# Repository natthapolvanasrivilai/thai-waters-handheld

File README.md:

# Thai Waters handheld

[**Current project status**](docs/wiki/Current-status.md) · [**Download the live interactive handbook**](https://github.com/natthapolvanasrivilai/thai-waters-handheld/releases/download/r0009-complete-fit-1/Thai-Waters-handbook.html) · [Hardware review PR #98](https://github.com/natthapolvanasrivilai/thai-waters-handheld/pull/98)

[Hardware closure and playtest issues](quality/hardware-gate.md) · [Product tracker](https://github.com/natthapolvanasrivilai/thai-waters-handheld/issues/1) · [November hardware review](quality/hardware-review-2026-11-23.md)

[Private touch playtest](https://thai-waters-pocket-angler.shoung0690.chatgpt.site) · [Builds and verification](docs/wiki/Software-and-tests.md#current-release) · [Clock and collection recovery](docs/wiki/Clock-and-saves.md)

[Hardware revisions and CAD](docs/wiki/Hardware-and-3D.md) · [One-unit BOM and price research](docs/wiki/BOM-and-business.md) · [Current release and hardware milestone](docs/wiki/Software-and-tests.md#current-release)

**[Browse the product wiki](docs/wiki/Home.md)** · **[Play on a phone](https://thai-waters-pocket-angler.shoung0690.chatgpt.site)**

[Rectangular PCB, revised mount and fit gauge](hardware/electronics/case-board-r0002/README.md) · [Open the new board review](https://github.com/natthapolvanasrivilai/thai-waters-handheld/releases/download/case-board-r0002-guide-2/Mount-review.html)

**Current PLA test print.** TW-A-0003-R0009 includes the rectangular PCB and matching case, all enclosure plastics and the PCB and component mockups. The 27 objects occupy eight plates for PolyTerra PLA on the X1 Carbon with a 0.4 mm nozzle and SuperTack. Physical fit awaits printing. [PolyTerra PLA X1C project](https://github.com/natthapolvanasrivilai/thai-waters-handheld/releases/download/r0009-complete-fit-1/Thai-Waters-R0009-Complete-Fit-PolyTerra-SuperTack-X1C.3mf) · [PLA print sequence and checks](hardware/mechanical/full-fit-r0009/README.md) · [Offline 3D assembly](https://github.com/natthapolvanasrivilai/thai-waters-handheld/releases/download/r0009-complete-fit-1/Enclosure-fit-guide.html)

Open the downloaded handbook in a browser. **Current status** checks this GitHub project on every open and links to the evidence for the selected revision. When the check fails, the handbook labels the dated snapshot saved with the file. The archived tabs still work offline. The [original R0011 handbook](https://github.com/natthapolvanasrivilai/thai-waters-handheld/releases/download/r0011-hardware-review-1/Thai-Waters-handbook.html) and [Rev F engineering release](https://github.com/natthapolvanasrivilai/thai-waters-handheld/releases/tag/rev-f-engineering-0.7) preserve their original evidence.

**Archived inert-print procedure · TW-A-0001-R0011.** Install the housing receiver-down, with both dovetail lips and the closed end resting on the first layer. Print the service cover and use both maximum-pack gauges. Measure receiver strength and check slide fit on the first article. [Archived print kit](https://github.com/natthapolvanasrivilai/thai-waters-handheld/releases/tag/r0011-receiver-toolpaths-2) · [Print and support-removal instructions](hardware/mechanical/TW-A-0001-R0011/PRINT-GUIDE.md)

Personal product project of GitHub user natthapolvanasrivilai. The handheld uses the top-left power key and screw-locked rod grip. It uses the Waveshare capacitive touchscreen controller module. Production disposition is HOLD for physical verification, supplier documentation and market classification.

| Stage | Working record |
|---|---|
| Hardware configuration | [Numeric assembly and part revision register](hardware/revisions/README.md) · [Hardware qualification and first-article status](quality/hardware-gate.md) |
| Product definition | [Requirements and status](product/requirements.md) |
| Industrial design and fit | [R0016 USB indicator entry](hardware/mechanical/TW-A-0001-R0016/README.md) · [R0015 power-key fit](hardware/mechanical/TW-A-0001-R0015/README.md) · [R0014 housing and A3 rails](hardware/mechanical/TW-A-0001-R0014/README.md) · [Seated R0013 connector and USB review](quality/seated-connector-review.md) · [R20 physical carrier fit](hardware/mechanical/pocket-reel-r19b-removal-trial/QA/R20-first-print/README.md) · [R0013 PCB fit kit and plate map](hardware/mechanical/pcb-fit-r0013/README.md) |
| Archived mechanical candidates | [R0011 receiver toolpaths](hardware/mechanical/TW-A-0001-R0011/README.md) · [Lower service cover and fitted STEP](hardware/mechanical/TW-A-0001-R0010/README.md) |
| Parts and procurement | [R0011 / R0004 engineering BOM](sourcing/production-intent/R0011-R0004-BOM.md) · [Line items and source evidence](sourcing/production-intent/R0011-R0004-engineering-BOM.csv) · [Cable routes and connections](hardware/electronics/harness-r0003/README.md) |
| Firmware and game content | [Arduino sketch](firmware/WillowCreek) · [Hosted browser and matching verification record](docs/wiki/Software-and-tests.md#current-release) · [Historical engineering downloads](docs/wiki/Software-and-tests.md#historical-builds) |
| Phone testing | [Private hosted game, QR and motion controls](game/sites/Phone-playtest.md) |
| Verification | [Prototype evidence](verification/fit-review.md) and [bench procedure](verification/bench-guide.md) |
| Market access | [Design and certification review](compliance/market-access.md) |
| Assembly and test | [Build traveler](manufacturing/build-traveler.csv) |
| Pilot, release and service | [Lifecycle gates](manufacturing/gates.md), [release index](releases/README.md), [service](service/README.md) |
| Revisions and third-party rights | [Change register](quality/changes.csv) and [provenance](third-party/NOTICE.md) |

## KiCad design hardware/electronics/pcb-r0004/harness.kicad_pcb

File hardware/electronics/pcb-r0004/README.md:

# A4 harness interposer for TW-A-0002-R0004

A4 carries the speaker attenuation resistors, the permanent I²C pull-ups and the autonomous remote power key. Its 13 surface-soldered wire lands connect to the A1 controller and the existing harness. The original J7 battery connector, J9 speaker plug and K3 switch stay available. Use the [editable KiCad project](harness.kicad_pro), [circuit drawing](circuit.pdf), [wire schedule](harness.csv) and [population BOM](bom.csv) together.

## Fabrication and assembly

The [engineering fabrication archive](harness-fab.zip) contains eight Gerber layers, the job file and metric Excellon. Fabricate the 23.00 × 13.00 mm outline on the Edge.Cuts centerline using 0.80 mm finished FR-4, two 35 µm outer copper layers, solder mask both sides and lead-free solderable finish. Plate the two Ø0.30 mm via holes. The back has no component lands or mask openings. Apply the top paste stencil to the 21 component pads. J1–J13 are integral 1.8 × 1.2 mm hand-solder lands. The quoted power rating for R1/R2 depends on local temperature and heat transfer into mounted copper. [Vishay rating conditions](https://www.vishay.com/docs/20035/dcrcwe3.pdf)

1. Orient the board component-side up with the four speaker lands at the left. R1 is the upper 2512 and R2 the lower. Across the top, R3 and R4 run left to right. At the bottom center R5 and R6 run left to right. D1 is the upper-right SOT23, Q1 the center device and Q2 the lower-right device. Their pin-1 markers sit to the left of their two-pin sides. Compare with the [placement coordinates](placement.csv).
2. Identify each controller net on the unpowered received A1. This layout uses the Waveshare V2 schematic. Record the controller revision. The published hardware tree supplies the V1/V2 schematics but omits production copper, board test points and controlled rework geometry. The [K3 contact drawing](../rev-f-power-key.md) distinguishes its raw switch contact from PWRON across R38. [Waveshare V2 schematic](https://github.com/waveshareteam/ESP32-S3-Touch-LCD-3.5B/blob/main/hardware/schematic/ESP32-S3-Touch-LCD-3.5B-V2-Schematic.pdf)
3. Retain the matching A1 J9 plug on the J1/J4 pair. Connect the free J2/J3 pair to the Adafruit 3923 speaker and trace polarity to its marked terminals. The two BTL legs float. At the loose A4, measure 4.99 Ω ±1% from J1 to J2 and from J4 to J3 after subtracting lead resistance. Check isolation of the two channels and ground. Normal speaker current passes through the resistors downstream of J9. A short at J9 or on the short input pigtail bypasses them. Its protection depends on the OEM PA. [Existing speaker specification](../usb-status-r0003/README.md)
4. Attach J5/J6/J7 to the fixed A1 end of W1. J8-27 on A1 is SDA, J8-31 is switched 3V3 and J8-25 is SCL. Retain W1 continuity to the encoder and W4 branch. Remove R1/R2 on the **A3 Boardoza board** and photograph the empty lands. With A4 isolated, measure 1.50 kΩ ±1% on each pull-up. Audit the assembled bus for fixed or accessory pulls and scope it at the furthest target. [Bus population and rise-time criteria](../integration-r0004/README.md)
5. A4 J8 receives A1 J8-1 raw USB VBUS. A4 J9 receives A1 J8-2 protected VBAT. Verify the two sources at their actual header positions before attaching the wires. On an A1 spin the J8-1 takeoff must remain upstream of the input limiter. D1 combines those two supplies only for the key gate network. J10/J11 go to the two remote SW1 contacts. J12/J13 go to the existing A1 K3 ground and raw switch contacts. Remove W3's previous direct raw-contact path. Leave R38 and K3 fitted. [BAV170 pinout](https://assets.nexperia.com/documents/data-sheet/BAV170.pdf) · [PMV65XP](https://assets.nexperia.com/documents/data-sheet/PMV65XP.pdf) · [PMV16XN](https://assets.nexperia.com/documents/data-sheet/PMV16XN.pdf)
6. Use the existing pigtails for the speaker and fine-stranded insulated leads for low-current signals. Preserve conductor identity at both ends. Lay the tinned conductor flat along each wire land with its jacket at the board edge. Keep all exposed strands within the pad and support each jacket off the solder joint. The simulation does not specify a physical cut length. Check jacket dimensions, anchor retention, removal stroke and clearance with the complete closed unit. The [populated STEP](harness.step) contains package models and copper. Its local bounds are X 0–23 mm, Y 0–13 mm, Z −0.035–1.995 mm. The STEP Y coordinate is 13 minus the Y value in the wire schedule.

## Verification

KiCad 10.0.8 reports zero ERC issues, zero PCB DRC errors or warnings, zero unconnected items and zero schematic parity differences. The two plated vias carry KEY_AON between sides. Independent Gerber/Excellon readback recovers all 14 networks and all 34 component/terminal pads. Minimum different-net copper spacing is 0.275 mm and copper-to-profile spacing is 0.550 mm. The parser gives a syntax warning for the location of the absolute-coordinate G90 statement in KiCad's Excellon output. It reads both metric drill coordinates and checks each against annular copper on both sides. [ERC](erc.json) · [DRC and parity](drc.json) · [Artwork reconstruction](artwork-verification.json)

The key study ran 84 operating cases and one deliberate open-wire control using ngspice 33. The supply cases cover a 3.0 V or 4.2 V cell alone, 4.75/5.00/5.25 V USB alone and two simultaneous source combinations. Each runs with both OEM K3 sensing topologies, 0.2 Ω and 10 kΩ closures, a 10 GΩ released contact, and 0.05/0.90 V diode-knee assumptions. Maximum simulated PWRON is 0.03657 V pressed and minimum PWRON is 3.30 V released. The lowest pressed key rail is 2.09995 V. Maximum modeled active source draw is 68.53 µA. Opening the VBUS feed with the cell absent leaves PWRON at 3.30 V despite a pressed remote key. [Case readings](key-corners.csv) · [Summary and engine hash](key-summary.json) · [Decks and solver logs](key-solver.zip)

The piecewise source model uses 2 Ω forward series resistance and a reverse-current slope of 80 nA per 5.25 V. The 0.90 V knee takes its scale from the specified BAV170 limit at 1 mA and 25 °C. The actual forward drop at microampere current varies with temperature. The fixtures retain the earlier level-1 MOSFET models, 3.3 V sense rail and assumed 50 kΩ PMIC pull-up. Confirm the actual autonomous key drive when A1 is asleep, off, charging or on USB alone, along with long-press timing and reverse current into an absent source. EC-01, EC-07 and EC-08 still require physical measurements. [First-article fixtures](../integration-r0004/first-article.csv)

A4 has no connection to connector CC, PMIC VBUS downstream of the entry network, ESP reset, regulator compensation, display enables, recovery UART or USB D+/D−. Those interfaces require separate controller circuitry. Existing power-step limits require the rail capacitor close to the MCU ground return and the battery capacitor close to J7. Their attachment impedance cannot be established on the A4 leads.

## Replay

Open the project in KiCad 10 with its stock symbol, footprint and STEP libraries installed. The saved schematic is directly editable. The [layout generator](layout.py) uses KiCad's bundled Python and can recreate the placed, routed PCB and three CSV tables. Use the following commands from this folder, supplying the KiCad installation's footprint folder as `FOOTPRINTS`. The local `TW.pretty` library supplies the wire land.

```text
<KiCad Python> layout.py --footprints <FOOTPRINTS>
kicad-cli sch erc --exit-code-violations --format json -o erc.json harness.kicad_sch
kicad-cli pcb drc --schematic-parity --all-track-errors --exit-code-violations --format json -o drc.json harness.kicad_pcb
kicad-cli pcb export gerbers --layers F.Cu,B.Cu,F.Mask,B.Mask,F.Silkscreen,B.Silkscreen,F.Paste,Edge.Cuts --no-protel-ext -o fab harness.kicad_pcb
kicad-cli pcb export drill --excellon-units mm -o fab harness.kicad_pcb
kicad-cli pcb export step --user-origin 0x13mm --include-pads --include-tracks --cut-vias-in-body --no-extra-pad-thickness -o harness.step harness.kicad_pcb
python verify_artwork.py harness-fab.zip
python key_corners.py --engine <ngspice-33>
```

Zip the contents of `fab` at the archive root to check newly plotted files. The independent checker uses Gerbonara 1.5.0 and Shapely 2.1.1. The [netlist](netlist.csv) indexes the component pad on each electrical network.

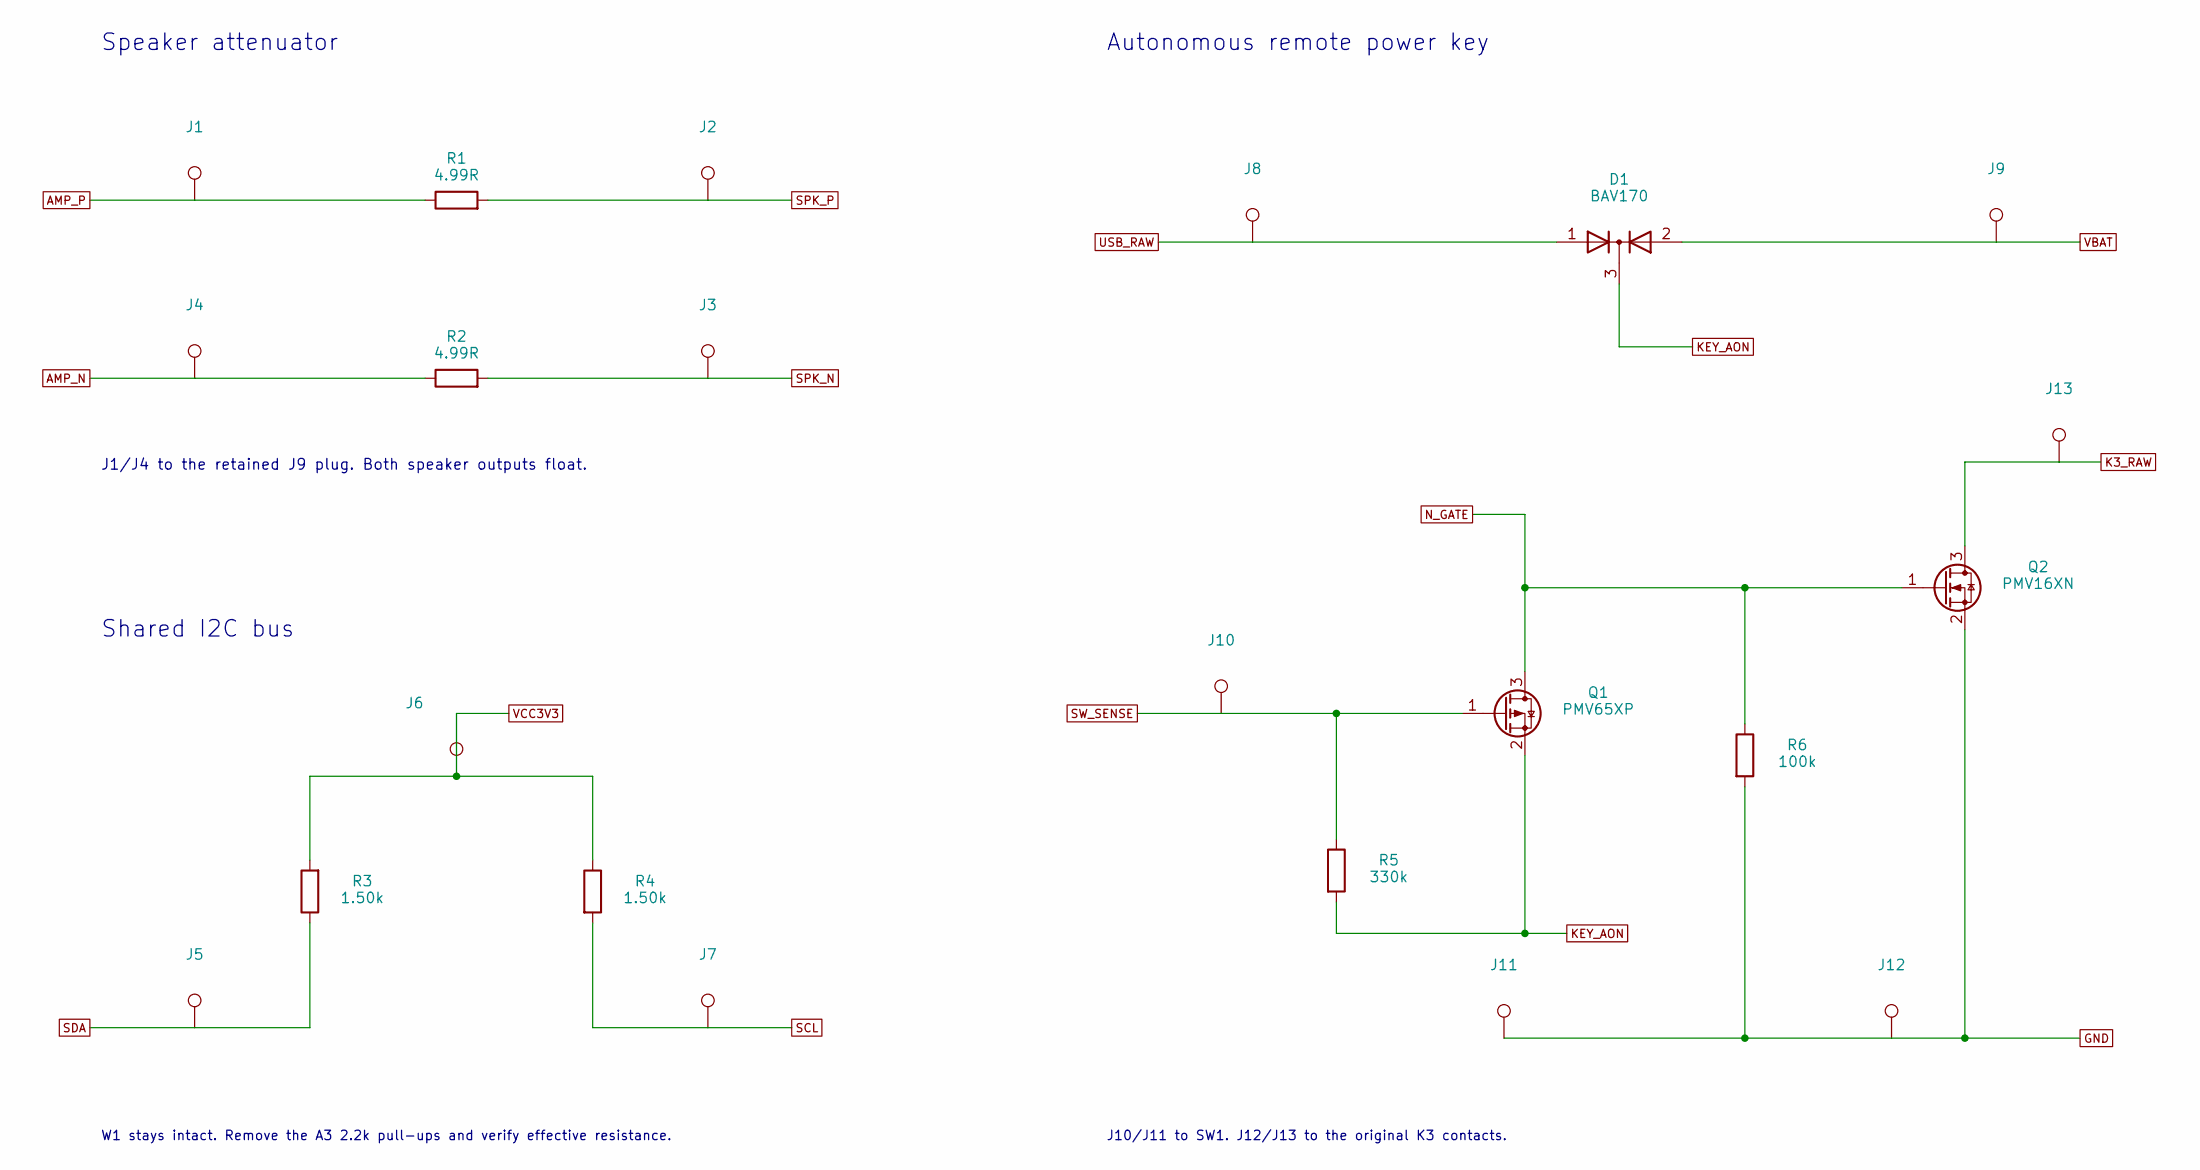
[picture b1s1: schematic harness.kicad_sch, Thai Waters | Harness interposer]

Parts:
D1: BAV170; SOT-23
J1: AMP_P; WireLand
J2: SPK_P; WireLand
J3: SPK_N; WireLand
J4: AMP_N; WireLand
J5: SDA; WireLand
J6: VCC3V3; WireLand
J7: SCL; WireLand
J8: USB_RAW; WireLand
J9: VBAT; WireLand
J10: SW_SENSE; WireLand
J11, J12: GND; WireLand
J13: K3_RAW; WireLand
Q1: PMV65XP; SOT-23
Q2: PMV16XN; SOT-23
R1, R2: 4.99R; R_2512_6332Metric
R3, R4: 1.50k; R_0603_1608Metric
R5: 330k; R_0603_1608Metric
R6: 100k; R_0603_1608Metric

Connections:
AMP_N: J4.1, R2.1
AMP_P: J1.1, R1.1
GND: J11.1, J12.1, Q2.2 (S), R6.2
K3_RAW: J13.1, Q2.3 (D)
KEY_AON: D1.3 (K), Q1.2 (S), R5.2
N_GATE: Q1.3 (D), Q2.1 (G), R6.1
SCL: J7.1, R4.2
SDA: J5.1, R3.1
SPK_N: J3.1, R2.2
SPK_P: J2.1, R1.2
SW_SENSE: J10.1, Q1.1 (G), R5.1
USB_RAW: D1.1 (A), J8.1
VBAT: D1.2 (A), J9.1
VCC3V3: J6.1, R3.2, R4.1

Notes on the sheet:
Speaker attenuator
J1/J4 to the retained J9 plug. Both speaker outputs float.
Shared I2C bus
W1 stays intact. Remove the A3 2.2k pull-ups and verify effective resistance.
Autonomous remote power key
J10/J11 to SW1. J12/J13 to the original K3 contacts.

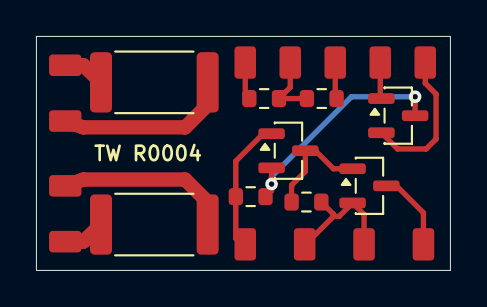
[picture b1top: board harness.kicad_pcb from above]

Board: 2 copper layers, 23.0 x 13.0 mm, 22 parts (0 on the bottom side), 14 nets.

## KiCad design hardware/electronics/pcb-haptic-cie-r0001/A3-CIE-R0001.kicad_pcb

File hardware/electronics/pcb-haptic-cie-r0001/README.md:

# A3 haptic daughterboard, CIE R0001

The editable [KiCad project](A3-CIE-R0001.kicad_pro) adapts the Boardoza DRV2605L R1.0 breakout to a five-position right-angle CviLux header. The new PCB has a 2.50 mm pitch, a ground trace from J1-2 to J1-5, and two unpopulated local pull-up positions. A4 supplies the shared bus pull-ups. This is a custom board. Purchasing the stock breakout supplies a different header and pitch. [Population and sourcing](bom.csv) · [Schematic](circuit.pdf) · [Boardoza upstream revision and license](../../components/boardoza-drv2605l/README.md)

## Identify the cable

With the installed board component-side up, J1-1 is the square pad at assembly X15.96 mm. Counting toward increasing assembly X, the row ends at X25.96 mm. The header opens toward +Y. Mark the VCC end before comparing the mating face and the wire-entry face, which mirror each other.

| Cavity | Board signal | Installed lead |
|---|---|---|
| 1 | VCC, regulated 3.3 V | W1 VCC tap |
| 2 | GND, grounding the driver's IN/TRIG input | Empty housing cavity, copper strap on PCB |
| 3 | SCL, U1 pin 2 | W1 SCL tap |
| 4 | SDA, U1 pin 3 | W1 SDA tap |
| 5 | GND, U1 pin 8 | W1 GND tap |

TP1 goes to motor OUT+, TP2 to OUT−. On an unpowered loose assembly check each cavity against the [schematic netlist](connectivity.xml), check ground between J1-2 and J1-5 with W4 removed, and check for adjacent shorts. Verify the CIE terminal, wire OD, crimp height, insulation grip, extraction force and polarity on the actual lot before electrical testing. CviLux specifies 19.6 N minimum crimp tensile strength for 26 AWG and an initial 10 mΩ maximum contact resistance under its dry-circuit test. The proposed W4 wire is Pico 8826-0-44. Usable service bend, delivered jacket OD, tooling and the crimp process remain open. [Terminal drawing](https://www.cvilux.com/uploads/drawings/101/749/CIEP06S.pdf) · [CviLux performance specification](https://www.cvilux.com/uploads/spec/101/753/SPCI172.pdf)

## Board and enclosure evidence

The engineering [Gerber and drill archive](A3-CIE-R0001-fab.zip) has five 1.00 mm J1 holes on 2.50 mm centers. The 20 × 20 mm board specifies 1.60 mm finished thickness. The nominal header drawing calls for finished holes Ø1.00 +0.10/−0.00 mm. Its unrestrained kinked end pins need insertion and post-solder inspection with the 1.40 mm insulating shim. Nominal straight-tail projection is approximately 0.4 mm below the finished board. The bare substrate STEP measures 1.51 mm, excluding the nominal outer layer stack. [Header drawing](https://www.cvilux.com/uploads/drawings/101/752/CIEP08S.pdf) · [Installed geometry](../harness-r0005/mate.py)

KiCad ERC found zero issues. DRC found zero unconnected items and zero schematic-parity issues. Three **unwaived courtyard errors** remain at the elevated J1. Its projected outline overlaps vacant R1 and populated C1/U1. With the nominal support installed, the housing-to-C1 and housing-to-U1 distances in the supplier geometry are 0.515 and 0.565 mm. Those distances depend on seating, board thickness and part tolerances. The physical shim, plug insertion, soldering and closed-case service check remain open. An independent check reconstructed all seven signal nets and 25 pads from fresh plotted copper and 14 plated drills. Two isolated fiducials carry no electrical pins. [ERC](erc.json) · [DRC](drc.json) · [Artwork evidence](artwork-verification.json)

Replacing the rectangular courtyard with the exact projected shroud would still intersect all three component courtyards. Extruding their KiCad XY bounds vertically through the supplier housing captured 6.343 mm³ at C1, 6.791 mm³ at R1 and 15.252 mm³ at U1. Clearing J1 in the positive PCB X direction requires moves exceeding 4.170, 4.170 and 4.425 mm respectively. The first two moves reach the opposite passive positions. Moving U1 also changes its ten pin routes and the registered populated CAD. A physical remedy requires a coordinated layout, component placement and service-path revision. The elevated approach remains a held alternative. [Relocation and clearance measurements](../../verification/r0012/courtyard-measurements.json)

## Source and reproduction

The symbol and footprint snapshots keep the source design editable with KiCad 10.0.8. The five-position header footprint was drawn from CviLux CIEP08SA. The upstream PCB, schematic geometry and TI package solid are adapted from Boardoza's DRV2605L project, licensed CC BY-SA 4.0. The derived Boardoza material is distributed under the [same license](LICENSE). The CviLux model is obtained from its manufacturer separately. The [model preparation script](make_models.py) builds the header model with its installed shim offset and recovers the TI device solids from the licensed Boardoza assembly. A clean native KiCad export produced 88 valid solids. The six header solids and fourteen fitted electronic solids matched the installed enclosure assembly in all bounding coordinates within 0.000001 mm. [Reconstruction evidence](../../verification/r0012/model-rebuild.json)

Use the [three-board verification instructions](../../verification/r0012/README.md) to regenerate the plot and rule checks. Loose-board order, powered bring-up and system acceptance remain on hold. No procurement quote or first article is recorded here.

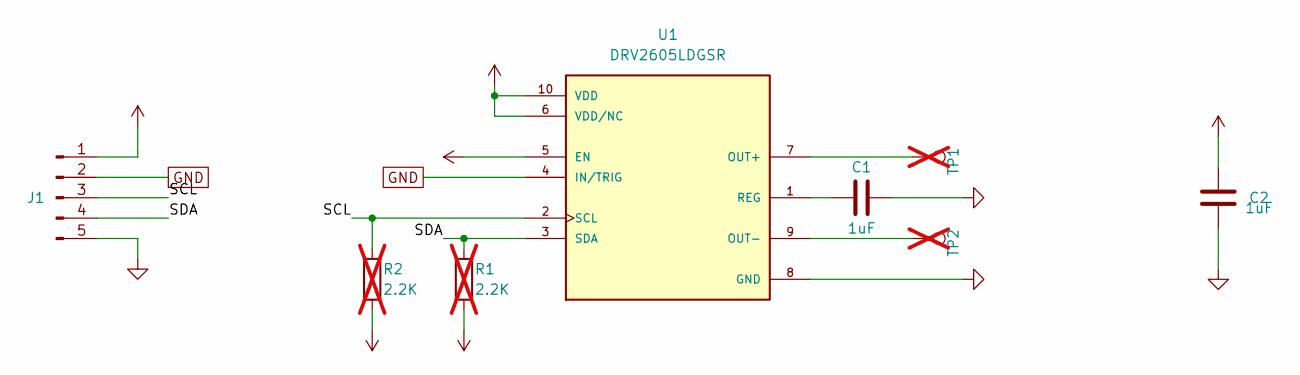
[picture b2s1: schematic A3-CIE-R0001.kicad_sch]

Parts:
C1, C2: 1uF; C_0603_1608Metric; MPN CL10A105KO8NNNC
J1: CIEP05P1HK0-NH; MPN CIEP05P1HK0-NH
R1, R2: 2.2K; R_0603_1608Metric; MPN CRT03F7E2201; not fitted
TP1, TP2: TestPoint; PinHeader_1x01_P2.54mm_Vertical; not fitted
U1: DRV2605LDGSR; SOP50P490X110-10N; PARTREV D

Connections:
/SCL: J1.3, R2.2, U1.2 (SCL)
/SDA: J1.4, R1.2, U1.3 (SDA)
GND: C1.2, C2.1, J1.2, J1.5, U1.4 (IN/TRIG), U1.8 (GND)
unnamed: TP1.1, U1.7 (OUT+)
unnamed: TP2.1, U1.9 (OUT-)
unnamed: C1.1, U1.1 (REG)
VCC: C2.2, J1.1, R1.1, R2.1, U1.5 (EN), U1.6 (VDD/NC), U1.10 (VDD)

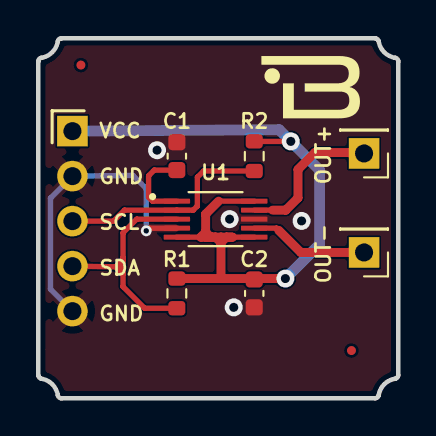
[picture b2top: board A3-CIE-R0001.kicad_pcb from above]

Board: 2 copper layers, 20.0 x 20.0 mm, 8 parts (0 on the bottom side), 7 nets.

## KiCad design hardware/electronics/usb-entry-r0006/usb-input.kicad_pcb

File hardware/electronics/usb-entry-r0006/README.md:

# A5 R0006 USB power entry

**TW-A5-USB-R0006 limits the intentional VBUS branches to 91.289 mA at 5.50 V, even if both pass FETs weld on.** On the same 15 Ω load, the corrected candidate drew 63.529 mA in simulation. The untouched factory control reproduced the original 348.837 mA failure. A positively identified Waveshare 3.5B V2 with LRC4 removed is required. [Schematic](circuit.pdf) · [KiCad project](usb-input.kicad_pro) · [Component schedule](bom.csv) · [Supplier pin list and board cut set](boundary.json)

## Source behavior

| Source | Available operation |
| --- | --- |
| No VBUS, ordinary USB-A to C connection, USB-C default Rp, unconfigured or 500 mA configured legacy host | The PMIC feed stays off. An operating unit runs from its battery. The blue lamp indicates connector power. The default-source suspend fixture stays below 2.5 mA. |
| Non-PD 5 V USB-C source advertising 1.5 A or 3 A on either orientation | A5 enables only the resistor-limited feed. The comparators work from VBUS with the processor off or the pack depleted. Type-C permits continued current under these advertisements during USB suspend. A return to default Rp withdraws the feed. |
| No battery and a 330 mA startup load | The rail misses the 3.9 V input floor. No-cell startup and single-cable flashing remain open. |

At AXP2101 input-regulation voltages of 4.2292–4.4908 V, the worst-drop circuit supplies **3.98–19.71 mA to the PMIC input** across 4.75–5.50 V. At 5.00 V that range is 7.86–11.94 mA. PMIC consumption and losses reduce what reaches the battery. An appropriate C-to-C charger can qualify without an awake processor or healthy pack. Positive battery charge current, charge termination, dead-pack recovery and off-state PMIC behavior need measurement. [AXP2101 input regulation](https://files.waveshare.com/wiki/common/X-power-AXP2101_SWcharge_V1.0.pdf) · [USB-IF Type-C functional tests, §4.6.1.1](https://www.usb.org/sites/default/files/USB%20Type%20C%20Functional%20Test%20Specification%202024%2003%2003.pdf) · [USB-IF suspend-current ECN](https://compliance.usb.org/index.asp?UpdateFile=Electrical)

## Connections and assembly

1. Identify the A1 lot and stuffing with USB and battery disconnected. The hash-checked V2 supplier schematic lists exactly three pins on VBUS′, J5-A4/B9, J5-A9/B4 and LRC4-1. The protected VBUS net contains LRC4-2, J8-1, D3-1, C20-2, C24-1 and AXP2101 UP1-37. Both OEM 10 µF capacitors belong on this protected side. The supplier STEP contains no LRC4 or BTREF1608A3R121 instance. A matched V2 land photo, physical access and registered land coordinates are outstanding. [Supplier V2 schematic](https://raw.githubusercontent.com/waveshareteam/ESP32-S3-Touch-LCD-3.5B/main/hardware/schematic/ESP32-S3-Touch-LCD-3.5B-V2-Schematic.pdf) · [Extracted boundary](boundary.json)
2. On an identified candidate, document both lands before and after LRC4 removal. With A5 disconnected, check breakout VBUS in both orientations to LRC4-1, J8-1 to LRC4-2, and isolation between the two halves in both meter polarities after capacitor settling. Verify separation from VBAT J8-2. Keep the stock ground ferrite LRC5 and both OEM 5.1 kΩ CC terminations. Inaccessible or ambiguous lands hold the article. [Point-to-point schedule](assembly.csv)
3. W1 joins LRC4-1. The ferrite FB1 then feeds exactly R2 and R9. The 62 Ω R2 branch feeds the new D1 TVS and common-source Q1/Q2 pair, returning through W2 to the fixed J8-1 solder tail. The 3.30 kΩ R9 branch feeds CTRL including U1/U2, their capacitors and the blue lamp. W3 goes to the fixed J8-3 ground tail. Remove the previous J8-1 lamp lead completely before connecting W7 to USB-PCB2. Replace the carrier's 2.70 kΩ resistor with 3.60 kΩ and check indicator visibility at the lower current. [Schematic](circuit.pdf) · [Installed wire geometry](installed-leads/README.md)
4. W4 senses R26-2/J5-A5 CC1. W5 senses R24-2/J5-B5 CC2. Each channel has its own 100 kΩ series tap, 10 MΩ pulldown and 10 nF filter. The two TLV3011B comparators share U1's 1.242 V reference through the 100 kΩ/110 kΩ divider. Either elevated CC voltage asserts an open-drain output. Q3 permits the gate pull-down when CTRL is present. The B-version comparators have fail-safe inputs and high-impedance outputs in power-on reset. W6 is an isolated spare pad. Check both physical terminations and orientation-specific results on the actual receptacle. No grant wire or firmware qualification is required. [Comparator pinout and POR](https://www.ti.com/lit/ds/symlink/tlv3011.pdf) · [CC voltage-band reference](https://www.ti.com/lit/ds/symlink/tusb320.pdf)
5. W2, W3 and W7 have installed conductor, insulation and solder geometry. W1 and the two CC taps lack registered V2 land locations. Their solder access, length, joint strain relief, ESD loop and service clearance remain open. Route only after matching the actual lot and support each fine land independently of the removable J8 plug. The raw conductor before the resistors needs insulation throughout. Its deliberate short is retained as a failing control. [Lead-fit scope](installed-leads/README.md)

## Routed board and circuit checks

The 23 × 16 × 0.8 mm PCB preserves all 17 R0004 footprint types, centers and rotations. KiCad 10.0.8 reported zero ERC, DRC, unrouted and schematic-parity issues. Independent Gerber and drill reconstruction recovered 17 nets, 60 pads and 38 plated holes. Minimum copper spacing was 0.25270 mm and copper-to-edge clearance was 0.63390 mm. The populated package and copper model contains 175 installed solids at X 13–36, Y 3–19 and Z 15.455–17.840 mm after the fixed 180° X rotation and (13,3,17.8) mm translation. [ERC](erc.json) · [DRC and parity](drc.json) · [Artwork check](artwork-verification.json) · [Fabrication plots for review](usb-input-fab.zip) · [Populated STEP](usb-input.step) · [Installed BREP](A5-power.brep)

The 65 ngspice cases produced 189 measurements. Of these, 175 met their limits, five characterize behavior, seven deliberately damaged or malformed fixtures failed and two no-cell loads missed the unchanged input-voltage floor. The replay rejects any unexpected disposition. [Measurements](measurements.csv) · [Solver and archive hashes](verification.json) · [Exact decks and logs](decks-and-logs.zip)

| Circuit check | Result |
| --- | --- |
| Same 15 Ω load | 63.529 mA on R0006 with an elevated advertisement. Refitting LRC4 gives 343.644 mA. The exact historical factory control gives 348.837 mA against the 100 mA limit. |
| Default advertisement and suspend, including a shorted lamp | At most 0.949 mA with the one active CC return at 0.61 V. Forcing both CC pins to the default maximum gives 1.070 mA including both. The downgrade fixture settles to 0.596 mA including CC. |
| 0.10 Ω short applied to an already charged, enabled output | Host current peaks at 68.039 mA in the 0.1/1.0 µH cable models. Downstream capacitors briefly supply around 44 A into the fault under the assumed ESR/ESL. This energy is local and its peak depends on the actual short-loop impedance. |
| Cold attach with both FETs welded, 5.50 V in 1 µs and 100 pF connector stray | 91.834 mA peak into the short. Integrated current above 100 mA over 20 ms is zero. With only the capacitive load the total charge across 20 ms is 154.9 µC, delivered below 100 mA. |
| 1 ns source edge with 500 pF raw stray capacitance | The instantaneous connector peak is 2.814 A. Total charge over 20 ns is 3.50 nC. Raw connector and wiring capacitance precedes the two ballasts. Measure its actual value and the real host edge independently. |
| Retained 330 mA-at-3.9 V no-cell dummy load | Essentially zero PMIC voltage on default Rp and 0.632 V on elevated Rp. |

The passive calculation is 5.50/(62 × 0.99) + 5.50/(3300 × 0.99) = 91.289 mA. Even connecting both resistors directly to ground keeps the intended VBUS branches within that bound. Connector parasitics and CC currents have their own reported quantities. Worst ideal R2 dissipation is 0.493 W. The model uses summed 70 °C routed copper, up to 75 mΩ per candidate fixed lead plus a conservative 75 mΩ return allowance, 0.25/0.65 Ω host loops and near-zero source resistance for stress. It includes both 110 nF CTRL decouplers, comparator/reference current, both CC returns, shorted and normal lamp, and 12 µF each for the two PMIC capacitors, with assumed 40 mΩ/10 nH each. Threshold guards include 1.209–1.274 V reference, ±0.35% divider legs, ±21 mV transfer error and 2 mV modeled hysteresis. The FETs and comparators are behavioral approximations. The attach-window charge and 50 µC screen are engineering measures. [Model and cases](verify_power.py) · [Copper extraction](copper.json)

A permanently asserted comparator can violate suspend while the independent resistor ceiling still holds. A missing OEM Rd under forced-live legacy VBUS can likewise make an over-range sense voltage look elevated. The threshold circuit has no USB-PD or debug-accessory decoder. Measure the response to USB PD signaling, changes in Rp, open CC, hot unplug, brownout and both orientations on the intended source set. Verify actual ESD behavior, resistor temperature, autonomous charging, lamp intensity and no current into the receptacle from a fitted pack. Instrument host current and local capacitor discharge separately. No physical USB compliance, charging or thermal qualification has occurred. [First-article criteria](../integration-r0004/first-article.csv)

Reproduce the electrical cut set with `python verify_boundary.py vendor-v2.pdf` and PyMuPDF. Run `python verify_power.py --engine PATH/TO/ngspice` for the routed circuit replay. The R0005 experiment preserves the prior active-switch short failure, and R0012 preserves the original factory fault injection. [R0005 rejected fast path](../usb-entry-r0005/README.md) · [R0012 evidence](../../verification/r0012/README.md)

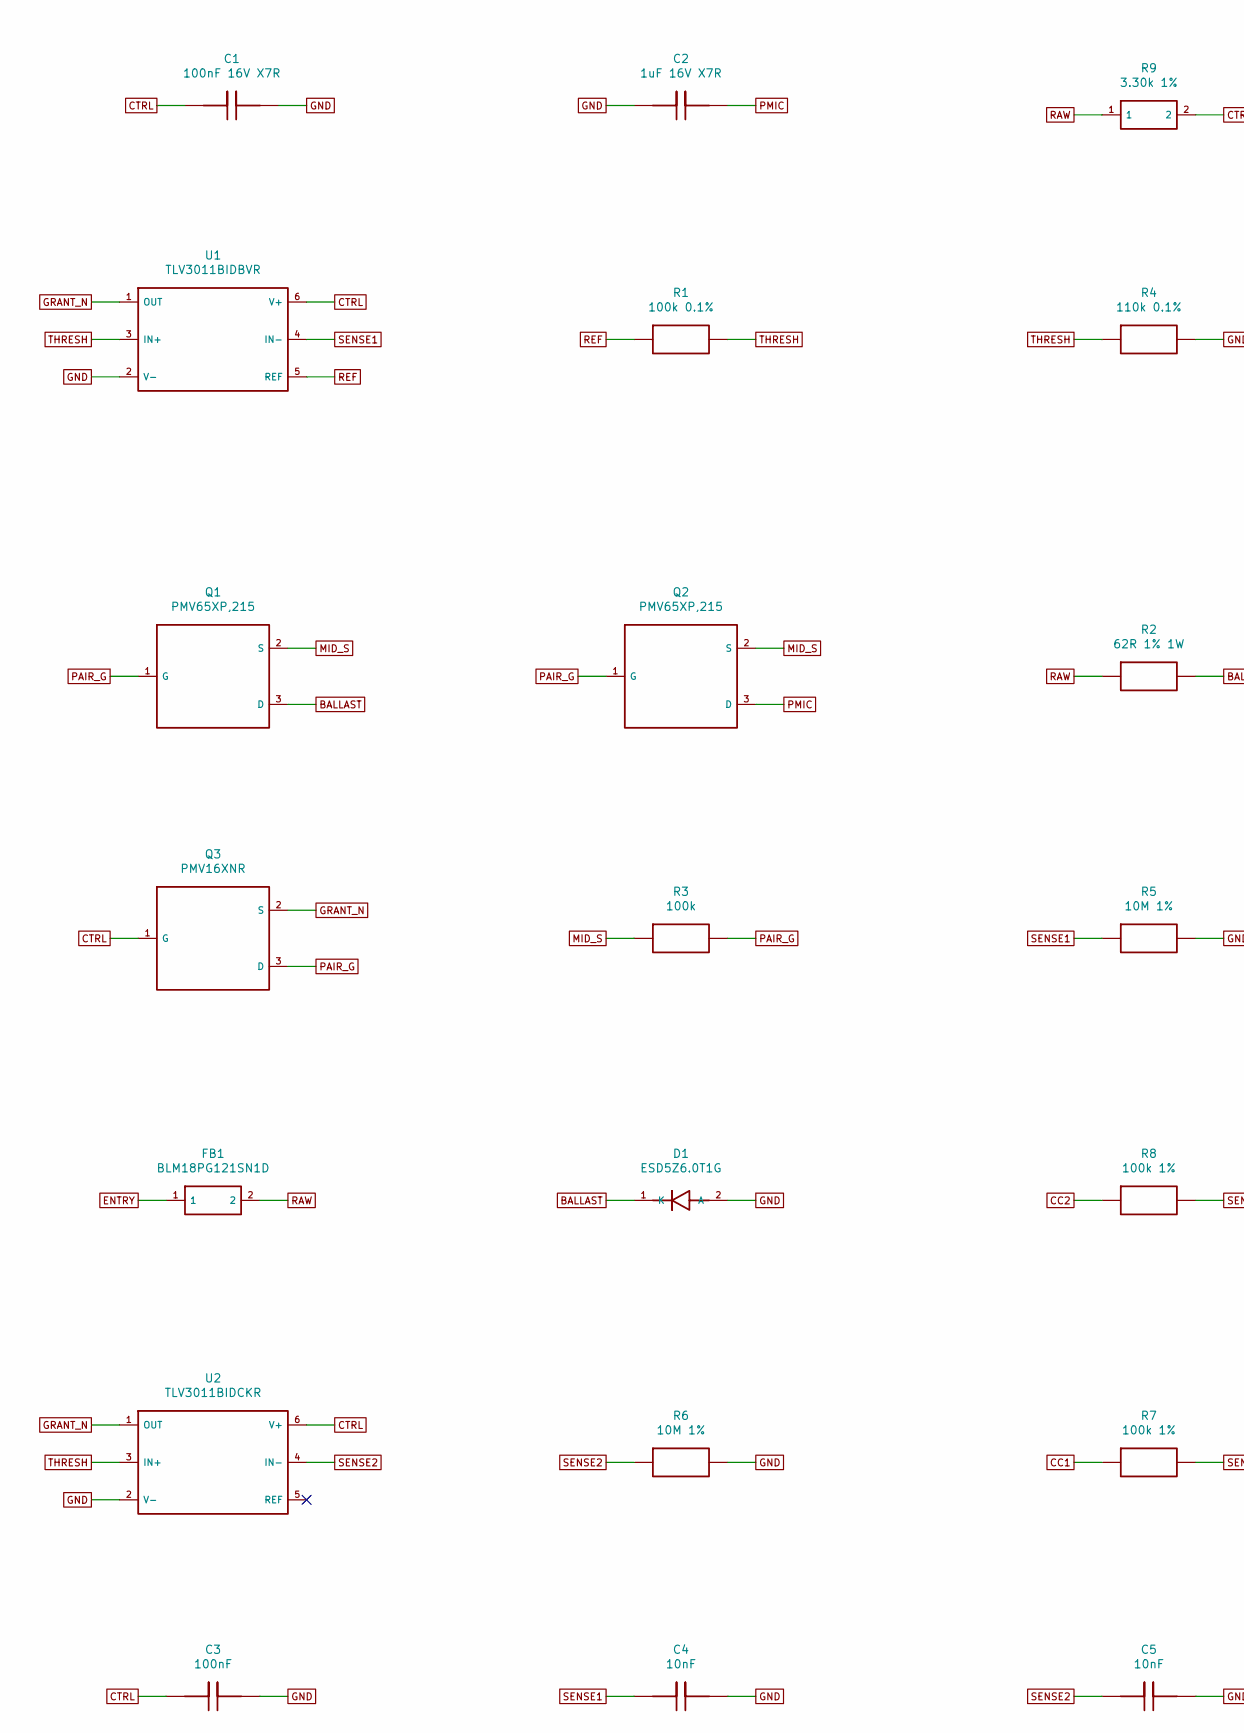
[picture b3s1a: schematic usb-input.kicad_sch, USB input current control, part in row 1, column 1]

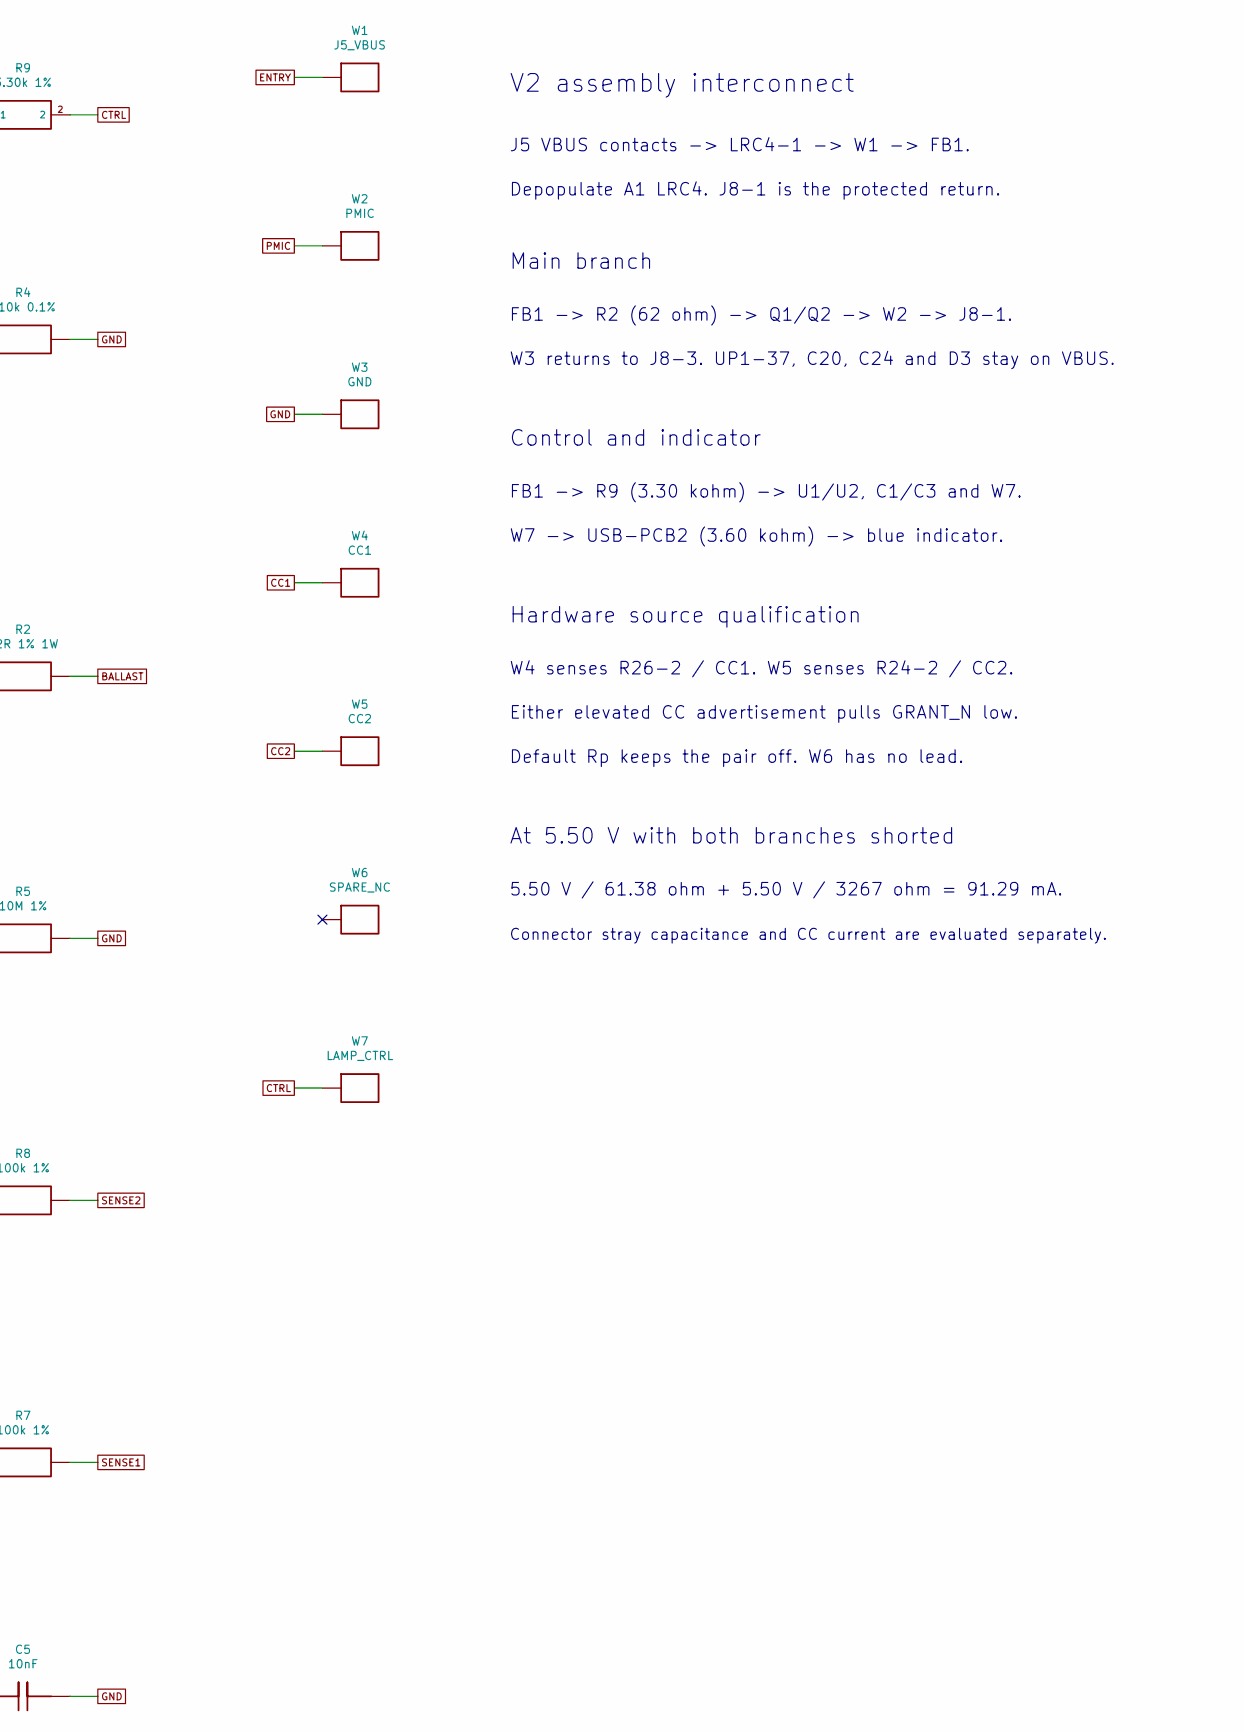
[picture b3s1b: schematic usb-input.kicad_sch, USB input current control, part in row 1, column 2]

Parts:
C1: 100nF 16V X7R; C_0603_1608Metric
C2: 1uF 16V X7R; C_0603_1608Metric
C3: 100nF; C_0402_1005Metric
C4, C5: 10nF; C_0402_1005Metric
D1: ESD5Z6.0T1G; D_SOD-523
FB1: BLM18PG121SN1D; L_0603_1608Metric
Q1, Q2: PMV65XP,215; SOT-23
Q3: PMV16XNR; SOT-23
R1: 100k 0.1%; R_0603_1608Metric
R2: 62R 1% 1W; R_2512_6332Metric
R3: 100k; R_0603_1608Metric
R4: 110k 0.1%; R_0603_1608Metric
R5: 10M 1%; R_0603_1608Metric
R6: 10M 1%; R_0402_1005Metric
R7, R8: 100k 1%; R_0402_1005Metric
R9: 3.30k 1%; R_0402_1005Metric
U1: TLV3011BIDBVR; SOT-23-6
U2: TLV3011BIDCKR; SOT-363_SC-70-6
W1: J5_VBUS; SolderWire-0.127sqmm_1x01_D0.48mm_OD1mm
W2: PMIC; SolderWire-0.127sqmm_1x01_D0.48mm_OD1mm
W3: GND; SolderWire-0.127sqmm_1x01_D0.48mm_OD1mm
W4: CC1; SolderWire-0.127sqmm_1x01_D0.48mm_OD1mm
W5: CC2; SolderWire-0.127sqmm_1x01_D0.48mm_OD1mm
W6: SPARE_NC; SolderWire-0.127sqmm_1x01_D0.48mm_OD1mm
W7: LAMP_CTRL; SolderWire-0.127sqmm_1x01_D0.48mm_OD1mm

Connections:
BALLAST: D1.1 (K), Q1.3 (D), R2.2
CC1: R7.1, W4.1
CC2: R8.1, W5.1
CTRL: C1.1, C3.1, Q3.1 (G), R9.2, U1.6 (V+), U2.6 (V+), W7.1
ENTRY: FB1.1, W1.1
GND: C1.2, C2.1, C3.2, C4.2, C5.2, D1.2 (A), R4.2, R5.2, R6.2, U1.2 (V-), U2.2 (V-), W3.1
GRANT_N: Q3.2 (S), U1.1 (OUT), U2.1 (OUT)
MID_S: Q1.2 (S), Q2.2 (S), R3.1
PAIR_G: Q1.1 (G), Q2.1 (G), Q3.3 (D), R3.2
PMIC: C2.2, Q2.3 (D), W2.1
RAW: FB1.2, R2.1, R9.1
REF: R1.1, U1.5 (REF)
SENSE1: C4.1, R5.1, R7.2, U1.4 (IN-)
SENSE2: C5.1, R6.1, R8.2, U2.4 (IN-)
THRESH: R1.2, R4.1, U1.3 (IN+), U2.3 (IN+)

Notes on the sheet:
V2 assembly interconnect
J5 VBUS contacts -> LRC4-1 -> W1 -> FB1.
Depopulate A1 LRC4. J8-1 is the protected return.
Main branch
FB1 -> R2 (62 ohm) -> Q1/Q2 -> W2 -> J8-1.
W3 returns to J8-3. UP1-37, C20, C24 and D3 stay on VBUS.
Control and indicator
FB1 -> R9 (3.30 kohm) -> U1/U2, C1/C3 and W7.
W7 -> USB-PCB2 (3.60 kohm) -> blue indicator.
Hardware source qualification
W4 senses R26-2 / CC1. W5 senses R24-2 / CC2.
Either elevated CC advertisement pulls GRANT_N low.
Default Rp keeps the pair off. W6 has no lead.
At 5.50 V with both branches shorted
5.50 V / 61.38 ohm + 5.50 V / 3267 ohm = 91.29 mA.
Connector stray capacitance and CC current are evaluated separately.

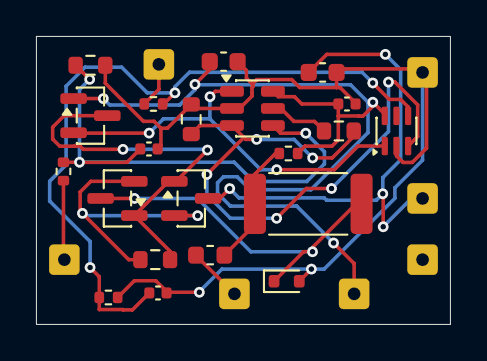
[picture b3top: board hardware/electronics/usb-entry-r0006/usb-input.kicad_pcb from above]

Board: 2 copper layers, 23.0 x 16.0 mm, 28 parts (0 on the bottom side), 15 nets.
